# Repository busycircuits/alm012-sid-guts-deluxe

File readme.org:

* ALM012 SID GUTS DELUXE

[[ALM012.png]]

** Introduction

The MOS Technology 6581/8580 ‘Sound Interface Device’ chip, aka the ‘SID’, was the sound generator chip used in the Commodore 64 home computer – the greatest selling home computer of all time.  The SID, by the means of 3 wavetable oscillators, a real analogue multi mode filter, an ADSR and various cross modulation options, provided the soundtrack to a generations gaming and perhaps many peoples first exposure to real sound synthesis. The SID’s unique musical aesthetic has lasted well beyond the lifetime of the C64 re-imagined in standalone products such as the SID Station and with in the computer via sophisticated software emulation.

The ALM Busy Circuits ‘SID GUTS DELUXE’ takes the legendary SID chip and brings it into the eurorack modular environment. By use of a real (or emulated) SID chip the classic sound is taken in a new direction with the levels of direct and voltage control only a modular system can offer.

The module features voltage control over numerous SID parameters including the classic PWM, Filter type, cut off, resonance and external input, waveform selection, secondary mod oscillator with ring and sync modulation, voltage per octave tracking and a 3 voice chord mode with inversion. 

The ‘SID GUTS DELUXE’ improves upon the original SID GUTS and was originally released 2014. In 2024 we ended production and have made the firmware and design files open source for anyone to build their own derivative. The files are available in this repository. 

Note you will need a donor SID chip for the module to work. Any real SID chip should work as should most emulated clones (Swin Sid etc). 

*PLEASE NOTE EVERYTHING IS PROVIDED AS IS. WE ARE UNABLE PROVIDE ANY SUPPORT TO ANYONE ATTEMPTING TO USE THESE FILES*

** Building and flashing the firmware

You'll need a basic 'usbtiny' AVR programmer.

You'll need to install avr-gcc and avrdude.

/(On mac using brew..)/
#+BEGIN_SRC
brew tap osx-cross/avr
brew install avr-gcc
brew install avrdude
#+END_SRC

Type 'make' in the firmare/ directory to compile the source code and
then run 'make ispload' (with your programmer connected) to program the
SID GUTS.

** License

Code: MIT license.

Hardware: cc-by-sa-3.0

** Guidelines for derivative works

*ALM is a registered trademark.*

The name "ALM" should not be used on any of the derivative works you create from these files.

We kindly ask to do not name any derivatives 'SID GUTS' but give it a new name.

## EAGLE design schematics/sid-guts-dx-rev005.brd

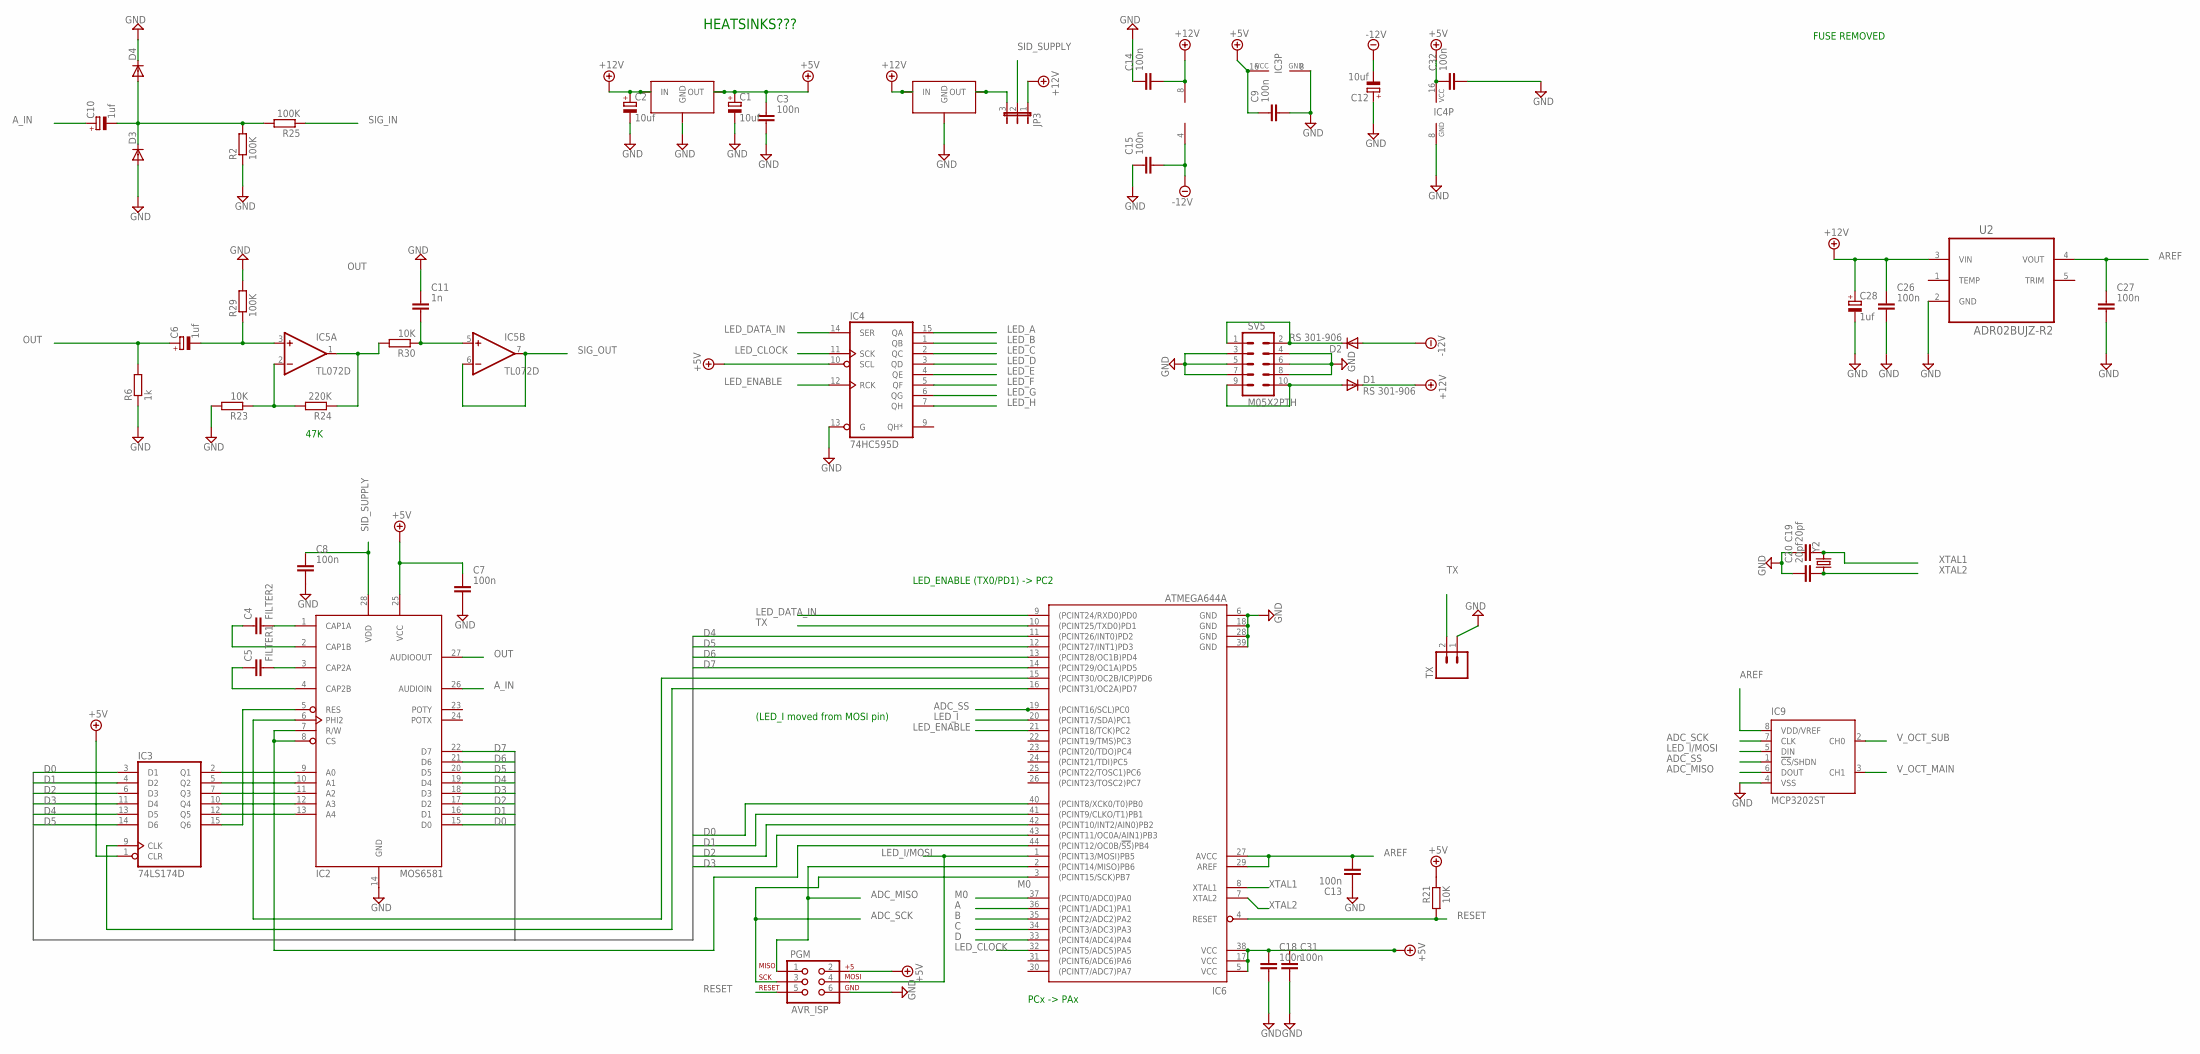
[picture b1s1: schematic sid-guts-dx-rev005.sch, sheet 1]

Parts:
C1, C2, C12: 10uf; PANASONIC_B
C3, C7, C8, C9, C13, C14, C15, C18, C26, C27, C31, C32: 100n; C0603
C4: FILTER2; C050-025X075
C5: FILTER1; C050-025X075
C6, C10, C28: 1uf; PANASONIC_B
C11: 1n; C0603
C19, C20: 20pf; C0603
D1, D2: RS 301-906; SMB-DIODE
D3, D4: DIODE-SOD123; SOD123
IC2: MOS6581; DIP-28
IC3: 74LS174D; SO16
IC4: 74HC595D; SO16
IC5: TL072D; SO08
IC6: ATMEGA644A; TQFP44
IC9: MCP3202ST; TSSOP8
JP3: JP2E; JP2
PGM: AVR_ISP; 2X3
R2, R25, R29: 100K; R0603
R6: 1k; R0603
R21, R23, R30: 10K; R0603
R24: 220K; R0603
SV5: M05X2PTH; AVR_ICSP
TX: M02PTH; 1X02
U2: ADR02BUJZ-R2; SOT95P280X100-5N
U3: 7805; VREG-7805-DPAK2
U4: 7905; VREG-7805-DPAK2
Y2: CRYSTALSMD; HC49UP

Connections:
+5V: C1.+, C3.1, C7.1, C9.1, C18.1, C31.1, C32.1, IC2.25 (VCC), IC3.1 (CLR), IC3.16 (VCC), IC4.10 (SCL), IC4.16 (VCC), IC6.5 (VCC), IC6.17 (VCC), IC6.38 (VCC), PGM.2, R21.2, U3.VOUT (OUT); also elsewhere on the board
+12V: C2.+, C14.2, C26.1, C28.+, D1.C, IC5.8 (V+), JP3.1, U2.3 (VIN), U3.VIN (IN), U4.VIN (IN); also elsewhere on the board
-12V: C12.-, C15.2, D2.A, IC5.4 (V-); also elsewhere on the board
A: IC6.36 ((PCINT1/ADC1)PA1); also elsewhere on the board
ADC_MISO: IC6.2 ((PCINT14/MISO)PB6), IC9.6 (DOUT), PGM.1
ADC_SCK: IC6.3 ((PCINT15/SCK)PB7), IC9.7 (CLK), PGM.3
ADC_SS: IC6.19 ((PCINT16/SCL)PC0), IC9.1 (!CS!/SHDN)
AREF: C13.2, C27.1, IC6.27 (AVCC), IC6.29 (AREF), IC9.8 (VDD/VREF), U2.4 (VOUT)
A_IN: C10.+, IC2.26 (AUDIOIN)
B: IC6.35 ((PCINT2/ADC2)PA2); also elsewhere on the board
C: IC6.34 ((PCINT3/ADC3)PA3); also elsewhere on the board
CS/RW: IC2.7 (R/W), IC2.8 (CS), IC6.44 ((PCINT12/OC0B/!SS!)PB4)
D: IC6.33 ((PCINT4/ADC4)PA4); also elsewhere on the board
D0: IC2.15 (D0), IC3.3 (D1), IC6.40 ((PCINT8/XCK0/T0)PB0)
D1: IC2.16 (D1), IC3.4 (D2), IC6.41 ((PCINT9/CLKO/T1)PB1)
D2: IC2.17 (D2), IC3.6 (D3), IC6.42 ((PCINT10/INT2/AIN0)PB2)
D3: IC2.18 (D3), IC3.11 (D4), IC6.43 ((PCINT11/OC0A/AIN1)PB3)
D4: IC2.19 (D4), IC3.13 (D5), IC6.11 ((PCINT26/INT0)PD2)
D5: IC2.20 (D5), IC3.14 (D6), IC6.12 ((PCINT27/INT1)PD3)
D6: IC2.21 (D6), IC6.13 ((PCINT28/OC1B)PD4)
D7: IC2.22 (D7), IC6.14 ((PCINT29/OC1A)PD5)
GND: C1.-, C2.-, C3.2, C7.2, C8.2, C9.2, C11.1, C12.+, C13.1, C14.1, C15.1, C18.2, C19.1, C20.1, C26.2, C27.2, C28.-, C31.2, C32.2, D3.A, D4.C, IC2.14 (GND), IC3.8 (GND), IC4.8 (GND), IC4.13 (G), IC6.6 (GND), IC6.18 (GND), IC6.28 (GND), IC6.39 (GND), IC9.4 (VSS), PGM.6, R2.1, R6.1, R23.2, R29.2, SV5.3, SV5.4, SV5.5, SV5.6, SV5.7, SV5.8, TX.1, U2.2 (GND), U3.GND, U4.GND; also elsewhere on the board
LED_A: IC4.15 (QA); also elsewhere on the board
LED_B: IC4.1 (QB); also elsewhere on the board
LED_C: IC4.2 (QC); also elsewhere on the board
LED_CLOCK: IC4.11 (SCK), IC6.32 ((PCINT5/ADC5)PA5)
LED_D: IC4.3 (QD); also elsewhere on the board
LED_DATA_IN: IC4.14 (SER), IC6.9 ((PCINT24/RXD0)PD0)
LED_E: IC4.4 (QE); also elsewhere on the board
LED_ENABLE: IC4.12 (RCK), IC6.21 ((PCINT18/TCK)PC2)
LED_F: IC4.5 (QF); also elsewhere on the board
LED_G: IC4.6 (QG); also elsewhere on the board
LED_H: IC4.7 (QH); also elsewhere on the board
LED_I: IC6.20 ((PCINT17/SDA)PC1); also elsewhere on the board
LED_I/MOSI: IC6.1 ((PCINT13/MOSI)PB5), IC9.5 (DIN), PGM.4
M0: IC6.37 ((PCINT0/ADC0)PA0); also elsewhere on the board
unnamed: D2.C, SV5.1, SV5.2
unnamed: JP3.3, U4.VOUT (OUT)
unnamed: D1.A, SV5.9, SV5.10
unnamed: C4.2, IC2.1 (CAP1A)
unnamed: C4.1, IC2.2 (CAP1B)
unnamed: C5.2, IC2.3 (CAP2A)
unnamed: C5.1, IC2.4 (CAP2B)
unnamed: IC2.9 (A0), IC3.2 (Q1)
unnamed: IC2.10 (A1), IC3.5 (Q2)
unnamed: IC2.11 (A2), IC3.7 (Q3)
unnamed: IC2.12 (A3), IC3.10 (Q4)
unnamed: IC2.13 (A4), IC3.12 (Q5)
unnamed: IC2.5 (RES), IC3.15 (Q6)
unnamed: IC5.1 (OUT), R24.1, R30.2
unnamed: IC3.9 (CLK), IC6.16 ((PCINT31/OC2A)PD7)
unnamed: C6.-, IC5.3 (+IN), R29.1
unnamed: IC5.2 (-IN), R23.1, R24.2
unnamed: IC2.6 (PHI2), IC6.15 ((PCINT30/OC2B/ICP)PD6)
unnamed: C10.-, D3.C, D4.A, R2.2, R25.2
unnamed: C11.2, IC5.5 (+IN), R30.1
OUT: C6.+, IC2.27 (AUDIOOUT), R6.2
RESET: IC6.4 (RESET), PGM.5, R21.1
SID_SUPPLY: C8.1, IC2.28 (VDD), JP3.2
SIG_IN: R25.1; also elsewhere on the board
SIG_OUT: IC5.6 (-IN), IC5.7 (OUT); also elsewhere on the board
TX: IC6.10 ((PCINT25/TXD0)PD1), TX.2
V_OCT_MAIN: IC9.3 (CH1); also elsewhere on the board
V_OCT_SUB: IC9.2 (CH0); also elsewhere on the board
XTAL1: C19.2, IC6.8 (XTAL1), Y2.2
XTAL2: C20.2, IC6.7 (XTAL2), Y2.1

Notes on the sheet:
47K
PCx -> PAx
FUSE REMOVED
HEATSINKS???
(LED_I moved from MOSI pin)
LED_ENABLE (TX0/PD1) -> PC2

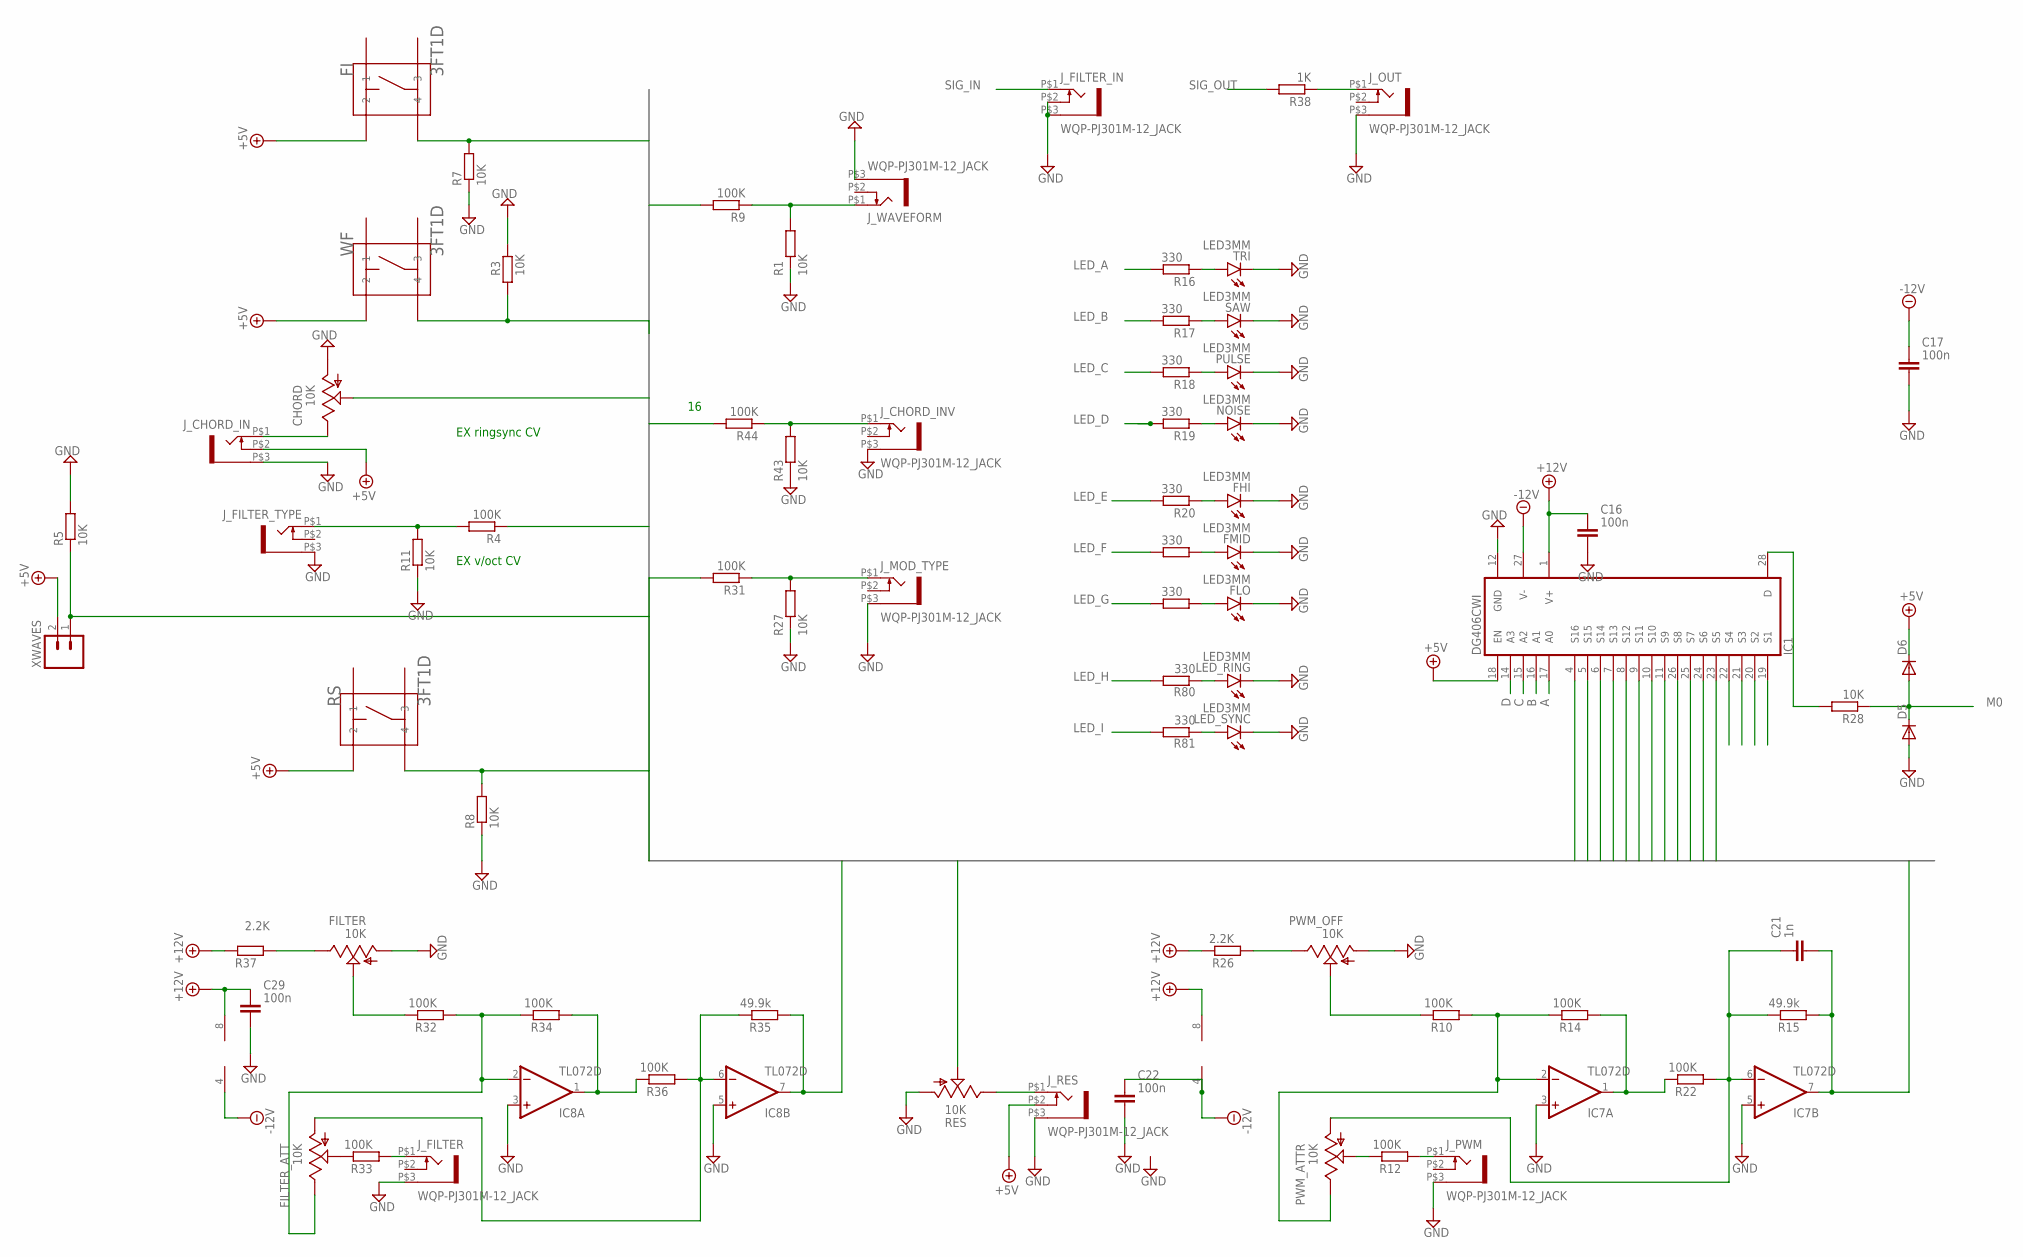
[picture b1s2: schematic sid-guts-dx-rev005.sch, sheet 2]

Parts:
C16, C17, C22, C29: 100n; C0603
C21: 1n; C0603
CHORD: 10K; EVUF
D5, D6: DIODE-SOD123; SOD123
FHI: LED3MM
FI: 3FT1D; 3FT
FILTER: 10K; EVUF
FILTER_ATT: 10K; EVUF
FLO: LED3MM
FMID: LED3MM
IC1: DG406CWI; SO28L
IC7, IC8: TL072D; SO08
J_CHORD_IN: WQP-PJ301M-12_JACK
J_CHORD_INV: WQP-PJ301M-12_JACK
J_FILTER: WQP-PJ301M-12_JACK
J_FILTER_IN: WQP-PJ301M-12_JACK
J_FILTER_TYPE: WQP-PJ301M-12_JACK
J_MOD_TYPE: WQP-PJ301M-12_JACK
J_OUT: WQP-PJ301M-12_JACK
J_PWM: WQP-PJ301M-12_JACK
J_RES: WQP-PJ301M-12_JACK
J_WAVEFORM: WQP-PJ301M-12_JACK
LED_RING: LED3MM
LED_SYNC: LED3MM
NOISE: LED3MM
PULSE: LED3MM
PWM_ATTR: 10K; EVUF
PWM_OFF: 10K; EVUF
R1, R3, R5, R7, R8, R11, R27, R28, R43: 10K; R0603
R4, R9, R10, R12, R14, R22, R31, R32, R33, R34, R36, R44: 100K; R0603
R15, R35: 49.9k; R0603
R16, R17, R18, R19, R20, R80, R81, R82, R83: 330; R0603
R26, R37: 2.2K; R0603
R38: 1K; R0603
RES: 10K; EVUF
RS: 3FT1D; 3FT
SAW: LED3MM
TRI: LED3MM
WF: 3FT1D; 3FT
XWAVES: M02PTH; 1X02

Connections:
+5V: D6.C, FI.P$2 (2), IC1.18 (EN), J_CHORD_IN.P$2 (3), J_RES.P$2 (3), RS.P$2 (2), WF.P$2 (2), XWAVES.2; also elsewhere on the board
+12V: C16.1, C29.1, IC1.1 (V+), IC7.8 (V+), IC8.8 (V+), R26.2, R37.2; also elsewhere on the board
-12V: C17.1, C22.1, IC1.27 (V-), IC7.4 (V-), IC8.4 (V-); also elsewhere on the board
A: IC1.17 (A0); also elsewhere on the board
B: IC1.16 (A1); also elsewhere on the board
C: IC1.15 (A2); also elsewhere on the board
D: IC1.14 (A3); also elsewhere on the board
EXP1: IC1.22 (S4)
EXP3: IC1.20 (S2)
EXP5: IC1.21 (S3)
EXP6: IC1.19 (S1)
GND: C16.2, C17.2, C22.2, C29.2, CHORD.1 (A), D5.A, FHI.K (C), FILTER.1 (A), FLO.K (C), FMID.K (C), IC1.12 (GND), IC7.3 (+IN), IC7.5 (+IN), IC8.3 (+IN), IC8.5 (+IN), J_CHORD_IN.P$3 (1), J_CHORD_INV.P$3 (1), J_FILTER.P$3 (1), J_FILTER_IN.P$2 (3), J_FILTER_IN.P$3 (1), J_FILTER_TYPE.P$3 (1), J_MOD_TYPE.P$3 (1), J_OUT.P$3 (1), J_PWM.P$3 (1), J_RES.P$3 (1), J_WAVEFORM.P$3 (1), LED_RING.K (C), LED_SYNC.K (C), NOISE.K (C), PULSE.K (C), PWM_OFF.1 (A), R1.1, R3.2, R5.2, R7.1, R8.1, R11.1, R27.1, R43.1, RES.1 (A), SAW.K (C), TRI.K (C); also elsewhere on the board
I5: C21.2, IC1.23 (S5), IC7.7 (OUT), R15.1
I6: IC1.24 (S6), RES.2 (S)
I7: IC1.25 (S7), IC8.7 (OUT), R35.1
I8: FI.P$4 (4), IC1.26 (S8), R7.2
I9: IC1.11 (S9), R5.1, XWAVES.1
I10: IC1.10 (S10), R8.2, RS.P$4 (4)
I11: IC1.9 (S11), R4.1
I12: CHORD.2 (S), IC1.8 (S12)
I13: IC1.7 (S13), R9.2
I14: IC1.6 (S14), R3.1, WF.P$4 (4)
I15: IC1.5 (S15), R31.2
I16: IC1.4 (S16), R44.2
LED_A: R16.2; also elsewhere on the board
LED_B: R17.2; also elsewhere on the board
LED_C: R18.2; also elsewhere on the board
LED_D: R19.2; also elsewhere on the board
LED_E: R20.2; also elsewhere on the board
LED_F: R83.2; also elsewhere on the board
LED_G: R82.2; also elsewhere on the board
LED_H: R80.2; also elsewhere on the board
LED_I: R81.2; also elsewhere on the board
M0: D5.C, D6.A, R28.1; also elsewhere on the board
unnamed: FHI.A, R20.1
unnamed: CHORD.3 (E), J_CHORD_IN.P$1 (2)
unnamed: FMID.A, R83.1
unnamed: FLO.A, R82.1
unnamed: IC1.28 (D), R28.2
unnamed: J_WAVEFORM.P$1 (2), R1.2, R9.1
unnamed: LED_RING.A, R80.1
unnamed: LED_SYNC.A, R81.1
unnamed: J_FILTER_TYPE.P$1 (2), R4.2, R11.2
unnamed: J_RES.P$1 (2), RES.3 (E)
unnamed: PWM_OFF.2 (S), R10.2
unnamed: IC7.2 (-IN), PWM_ATTR.3 (E), R10.1, R14.2
unnamed: R16.1, TRI.A
unnamed: R17.1, SAW.A
unnamed: PULSE.A, R18.1
unnamed: NOISE.A, R19.1
unnamed: J_PWM.P$1 (2), R12.1
unnamed: PWM_ATTR.2 (S), R12.2
unnamed: IC7.1 (OUT), R14.1, R22.2
unnamed: C21.1, IC7.6 (-IN), PWM_ATTR.1 (A), R15.2, R22.1
unnamed: PWM_OFF.3 (E), R26.1
unnamed: J_MOD_TYPE.P$1 (2), R27.2, R31.1
unnamed: FILTER.2 (S), R32.2
unnamed: FILTER_ATT.3 (E), IC8.2 (-IN), R32.1, R34.2
unnamed: J_FILTER.P$1 (2), R33.1
unnamed: IC8.1 (OUT), R34.1, R36.2
unnamed: FILTER_ATT.1 (A), IC8.6 (-IN), R35.2, R36.1
unnamed: FILTER.3 (E), R37.1
unnamed: J_OUT.P$1 (2), R38.1
unnamed: FILTER_ATT.2 (S), R33.2
unnamed: J_CHORD_INV.P$1 (2), R43.2, R44.1
SIG_IN: J_FILTER_IN.P$1 (2); also elsewhere on the board
SIG_OUT: R38.2; also elsewhere on the board

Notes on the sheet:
EX v/oct CV
EX ringsync CV

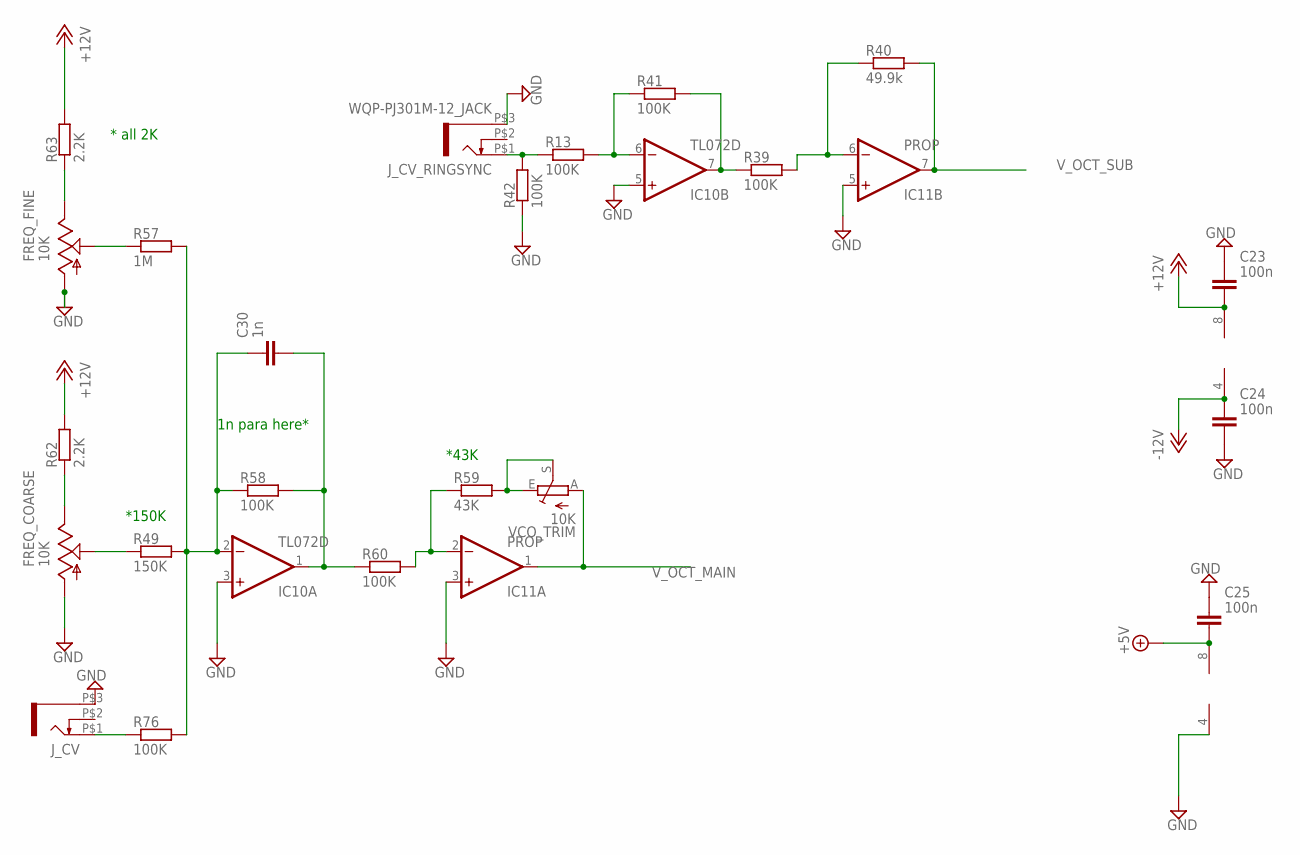
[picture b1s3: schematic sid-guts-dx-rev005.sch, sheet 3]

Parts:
C23, C24, C25: 100n; C0603
C30: 1n; C0603
FREQ_COARSE: 10K; EVUF
FREQ_FINE: 10K; EVUF
IC10: TL072D; SO08
IC11: PROP; SO08
J_CV: WQP-PJ301M-12_JACK
J_CV_RINGSYNC: WQP-PJ301M-12_JACK
R13, R39, R41, R42, R58, R60, R76: 100K; R0603
R40: 49.9k; R0603
R49: 150K; R0603
R57: 1M; R0603
R59: 43K; R0603
R62, R63: 2.2K; R0603
VCO_TRIM: 10K; S64YW

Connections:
+5V: C25.2, IC11.8 (V+); also elsewhere on the board
+12V: C23.2, IC10.8 (V+), R62.2, R63.2; also elsewhere on the board
-12V: C24.1, IC10.4 (V-); also elsewhere on the board
GND: C23.1, C24.2, C25.1, FREQ_COARSE.1 (A), FREQ_FINE.1 (A), IC10.3 (+IN), IC10.5 (+IN), IC11.3 (+IN), IC11.4 (V-), IC11.5 (+IN), J_CV.P$3 (1), J_CV_RINGSYNC.P$3 (1), R42.1; also elsewhere on the board
unnamed: IC10.7 (OUT), R39.1, R41.2
unnamed: IC10.6 (-IN), R13.2, R41.1
unnamed: J_CV_RINGSYNC.P$1 (2), R13.1, R42.2
unnamed: IC11.6 (-IN), R39.2, R40.1
unnamed: J_CV.P$1 (2), R76.1
unnamed: FREQ_COARSE.2 (S), R49.1
unnamed: C30.1, IC10.2 (-IN), R49.2, R57.2, R58.1, R76.2
unnamed: FREQ_FINE.2 (S), R57.1
unnamed: C30.2, IC10.1 (OUT), R58.2, R60.1
unnamed: IC11.2 (-IN), R59.1, R60.2
unnamed: R59.2, VCO_TRIM.E, VCO_TRIM.S
unnamed: FREQ_COARSE.3 (E), R62.1
unnamed: FREQ_FINE.3 (E), R63.1
V_OCT_MAIN: IC11.1 (OUT), VCO_TRIM.A; also elsewhere on the board
V_OCT_SUB: IC11.7 (OUT), R40.2; also elsewhere on the board

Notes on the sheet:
*43K
* all 2K
1n para here*
*150K

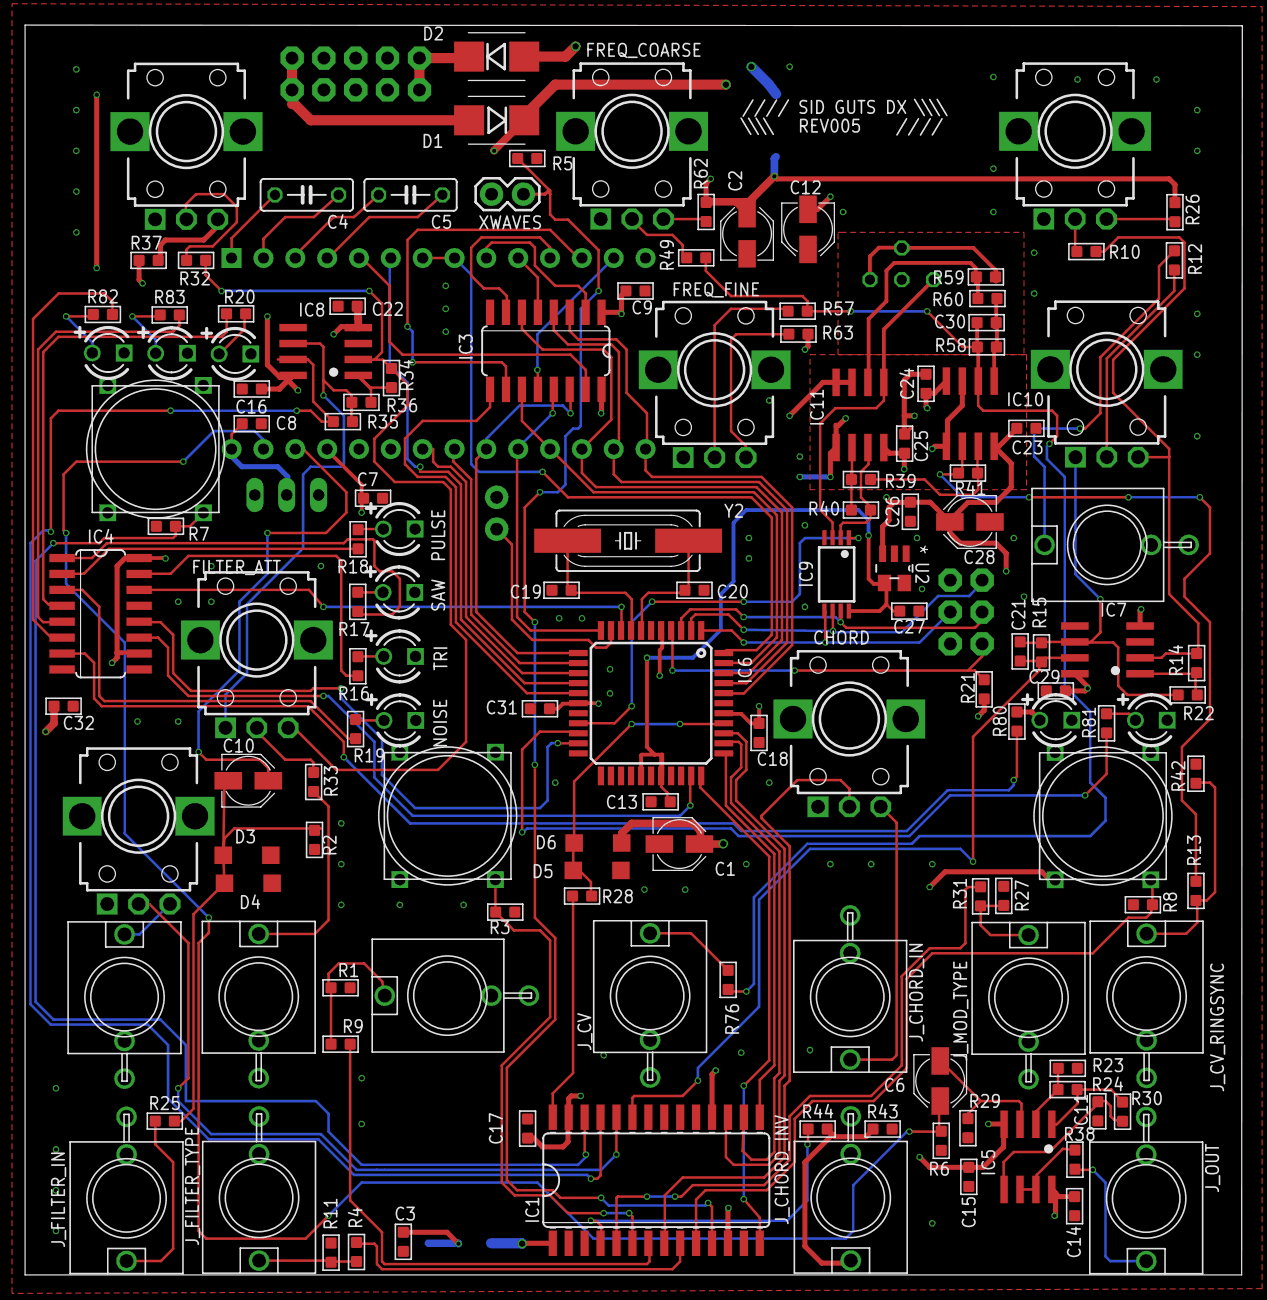
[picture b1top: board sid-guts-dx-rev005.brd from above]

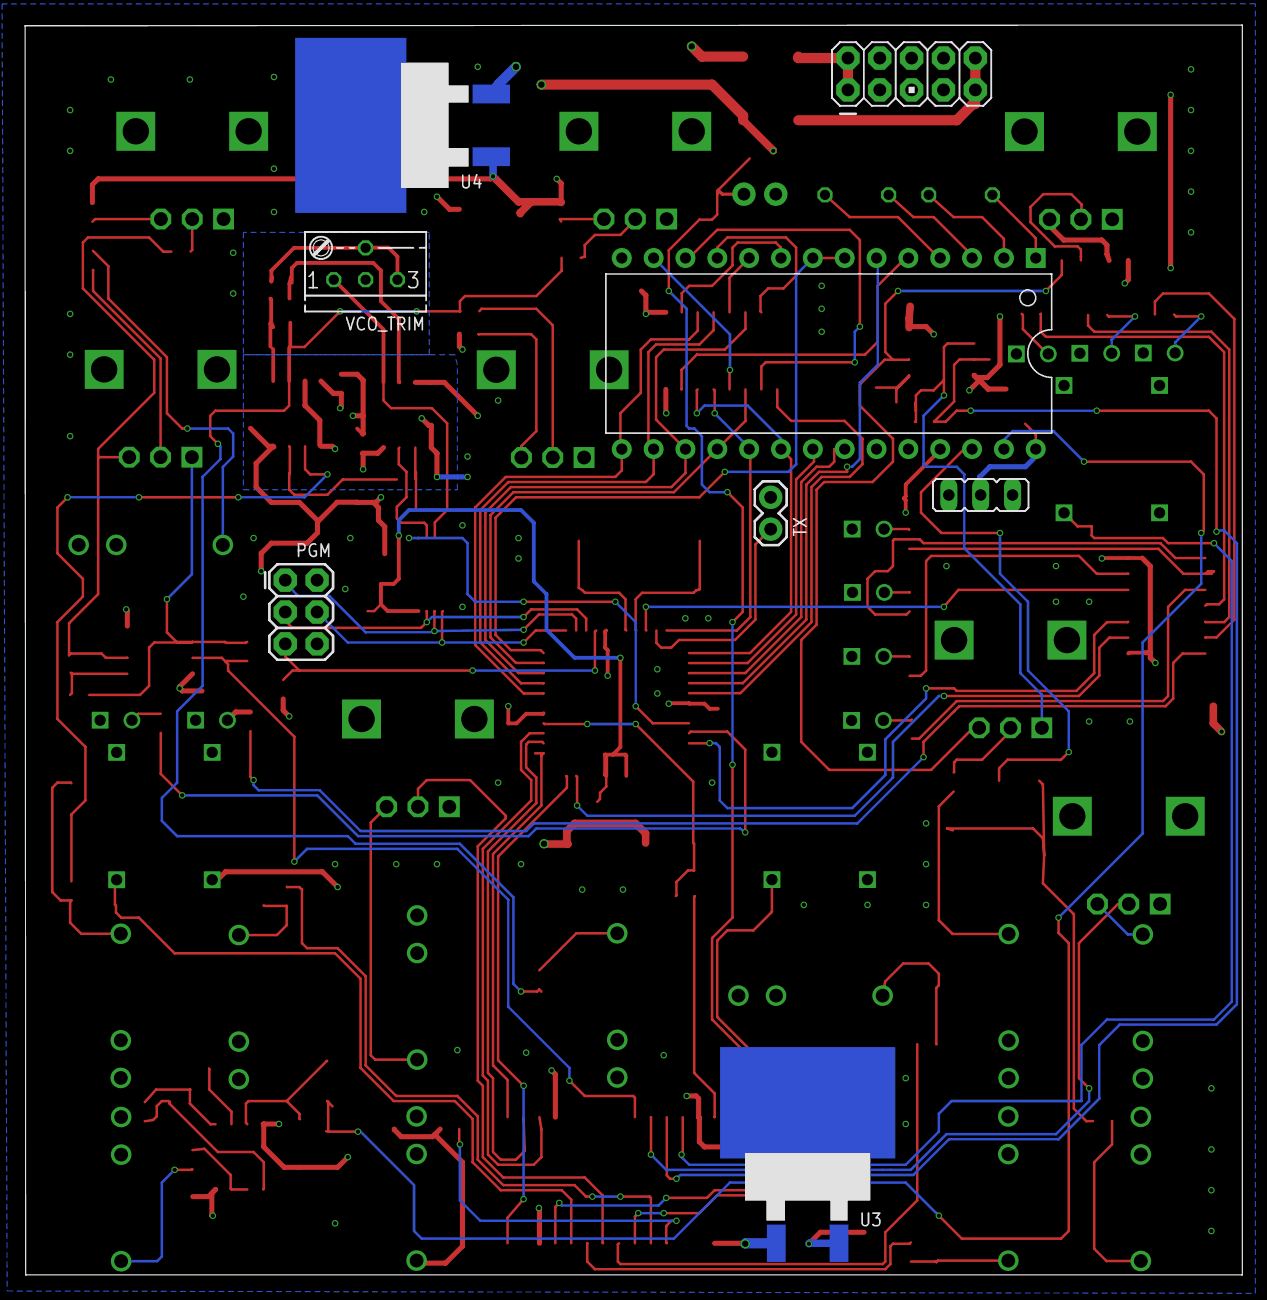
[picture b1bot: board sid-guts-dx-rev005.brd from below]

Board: 4 copper layers, 97.1 x 99.7 mm, 147 parts (8 on the bottom side), 122 nets.

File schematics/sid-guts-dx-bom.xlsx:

Qty | Parts | Value | Device | Package | SOLDERED REAR | Description / Notes | Mouser Part Num | RS Part Num | Other Part Num
7 | CHORD, FILTER, FILTER_ATT, FREQ_COARSE, PWM_ATTR, PWM_OFF, RES | 10K | ALPHA-9MMA | EVUF |  | 9 mm Square Rotary Potentiometers
1 | FREQ_FINE | 10K | ALPHA-9MMA |  |  | knurled 9 mm Square Rotary Potentiometer
1 | VCO_TRIM | 10K | TRIM_1234-S64YW | S64YW | Y | Trimmer | 72-T93YB-10K
22 | R2, R4, R9, R10, R12, R13, R14, R22, R25, R29, R31, R32, R33, R34, R36, R39, R4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 | 100K | RESISTOR0603 | R0603
1 | R49 | 150k | RESISTOR0603 | R0603
12 | R1, R3, R5, R7, R8, R11, R21, R23, R27, R28, R30, R43 | 10K | RESISTOR0603 | R0603
1 | R24 | 200K | RESISTOR0603 | R0603
9 | R80, R81, R82, R83, R16, R17, R18, R19, R20 | 330 | RESISTOR0603 | R0603
4 | R26, R37, R63, R62 | 2.2K | RESISTOR0603 | R0603
1 | R38 | 1K | RESISTOR0603 | R0603
1 | R57 | 1M | RESISTOR0603 | R0603
1 | R6 | 1k | RESISTOR0603 | R0603
3 | R15, R35, R40 | 49.9k | RESISTOR0603 | R0603
1 | R59 | 43K | RESISTOR0603 | R0603
19 | C3, C7, C8, C9, C13, C14, C15, C16, C17, C18, C22, C23, C24, C25, C26, C27, C29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 | 100n | CAPACITOR0603 | C0603
3 | C30, C11, C21 | 1n | CAPACITOR0603 | C0603
3 | C6, C10, C28 | 1uf | CPOL-EUB | PANASONIC_B |  | POLARIZED CAPACITOR, European symbol
3 | C1, C2, C12 | 10uf | CPOL-EUB | PANASONIC_B |  | POLARIZED CAPACITOR, European symbol
2 | C19, C20 | 18pf | CAPACITOR0603 | C0603
1 | IC4 | 74HC595D | 74HC595D | SO16 |  | 8-bit SHIFT REGISTER, output latch | 511-M74HC595YRM13TR
1 | IC3 | 74LS174D | 74LS174D | SO16 |  | Hex D type FLIP FLOP, clear |  |  | Farnell 175-0034
1 | IC6 | ATMEGA644A | ATMEGA644A | TQFP44 |  | ATMEGA644PV-10AU |  | 715-3814 | Farnell 1972104
1 | IC1 | DG406CWI | DG406CWI | SO28L |  | ANALOG MULTIPLEXER | 781-DG406DW-E3
4 | IC5, IC7, IC8, IC10 | TL072D | TL072D | SO08 |  | OP AMP | 595-TL072CDR
1 | IC9 | MCP3202ST | MCP3202ST | TSSOP8 |  | MCP3202-CI/ST Dual Channel 12-Bit A/D Converter with SPI Serial Interface | 579-MCP3202-CI/ST
1 | IC2 | SOCKET | MOS6581 | DIL-28 | Y | DIL-28 Wide SOCKET - No IC |  |  | Rapid 22-0115
1 | IC11 | PROP | AD8532 | SO08 |  | OP AMP | 584-AD8532ARZ-R
1 | U3 | 7805 | VREG-7805-DPAK2 | VREG-7805-DPAK2 | Y |  |  | 714-0657
1 | U4 | 7809 | VREG-7809-DPAK2 | VREG-7809-DPAK2 | Y |  | 511-L7809CD2T-TR
1 | U2 | ADR02BUJZ-R2 | ADR02BUJZ-R2 | TSOT-5 ? |  | ADR02BUJZ-R2 Ultracompact, Precision 5.0 Voltage References |  |  | This should be ADR02AUJZ-REEL7
2 | D1, D2 | RS 301-906 | DIODESMB | SMB-DIODE |  | Diode | 621-B130LB-F
2 | D3, D4, |  | DIODE-SOD123 | SOD123 |  | DIODE |  | 700-3671
2 | D5, D6 |  |  | SOD123 |  | Diode | 512-MBR0520L
9 | FHI, FLO, FMID, LED_RING, LED_SYNC, NOISE, PULSE, SAW, TRI | LED3MM | LED3MM | LED3MM |  | All RED except NOISE green, TRI yellow, SAW orange
1 | SV5 | M05X2PTH | M05X2PTH |  | Y | Header 5x2
1 | Y2 |  | CRYSTALSMD | HC49UP |  | 16 Mhz Crystal |  |  | Farnell 184-2294
1 | JP3 |  | JP3E | JP3 | Y | 3 Pin header for jumper
2 | C4, C5 |  |  |  | Y | Capacitor SOCKET - 2.54MM SINGLE ROW HEADER 3 PIN with middle pin clipped.
3 | FI, RS, WF | 3FT1D | 3FT1D | 3FT |  | Mulitmec - 3FT1D
12 | J_CHORD_INV, J_CV_RINGSYNC, J_FILTER, J_FILTER_IN, J_MOD_TYPE, J_OUT, J_PWM, J_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 | WQP-PJ301M-12_JACK | WQP-PJ301M-12_JACK | WQP-PJ301M-12_JACK |  | Jacks
2 | TX, XWAVES |  | M02PTH | 1X02 |  | NOT NEEDED
1 | PGM | AVR_ISP | AVR_SPI_PRG_6PTH | 2X3 |  | NOT NEEDED

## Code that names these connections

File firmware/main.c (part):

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#define PIN_MULT_B PIN_A2 
#define PIN_MULT_C PIN_A3
#define PIN_MULT_D PIN_A4 
#define PIN_LED_I      PIN_C1 
#define PIN_LED_DATA   PIN_D0
#define PIN_LED_CLOCK  PIN_A5
#define PIN_LED_ENABLE PIN_C2
#define PIN_TX PIN_D1

#define PIN_ADC_MOSI     PIN_B5
#define PIN_ADC_MISO     PIN_B6
#define PIN_ADC_SPICLOCK PIN_B7
#define PIN_ADC_SLAVE_SELECT PIN_C0

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void mcp3202_init()
{
  uu_pin_mode(PIN_ADC_MOSI, OUTPUT);
  uu_pin_mode(PIN_ADC_MISO, INPUT);
  uu_pin_mode(PIN_ADC_SPICLOCK, OUTPUT);
  uu_pin_mode(PIN_ADC_SLAVE_SELECT, OUTPUT);
}
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  //read bits from adc
  for (int i=11; i>=0; i--)
    {
      adcvalue += uu_pin_digital_read(PIN_ADC_MISO)<<i;
      //cycle clock
      uu_pin_digital_write(PIN_ADC_SPICLOCK, HIGH);
      uu_pin_digital_write(PIN_ADC_SPICLOCK, LOW);
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  byte shift_mask = mask & 0xFF;

  if (mask & LED_SYNC)
    uu_pin_digital_write(PIN_LED_I, HIGH);
  else
    uu_pin_digital_write(PIN_LED_I, LOW);

  uu_pin_digital_write(PIN_LED_ENABLE, LOW);
  uu_pin_shift_out(PIN_LED_DATA, PIN_LED_CLOCK, MSBFIRST, shift_mask);  
  uu_pin_digital_write(PIN_LED_ENABLE, HIGH);
}

int analog_read()
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  int c, i = 0;

  PORTD = 0;
  PORTB = 0x10;   // PB4 is high to disable Chip Select
  DDRD  = 0xFE;   // Keep RxD as an input, everything else output
  DDRB  = 0xFF;

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
  uu_usart_init();
  
  uu_pin_mode(PIN_LED_I, OUTPUT);

  uu_pin_mode(PIN_MULT_IN, INPUT);

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  uu_pin_mode(PIN_MULT_D, OUTPUT);

  uu_pin_mode(PIN_LED_DATA, OUTPUT);
  uu_pin_mode(PIN_LED_CLOCK, OUTPUT);
  uu_pin_mode(PIN_LED_ENABLE, OUTPUT);
  
  /* Initialise Timer 0 OC0A to 1MHz on Pin 6. */
  TIMSK2 = 0;
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
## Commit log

2024-05-01 fix image ref and typo
2024-05-01 more cleanups
2024-05-01 and more misc cleanups...
2024-05-01 fix version typo in source

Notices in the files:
firmware/main.c:
Copyright (c) 2014 ALM Co Ltd
Parts based on code written by Alexis Kotlowy, released in Public Domain.
parts and their libraries:
SparkFun: Licensing: CC v3.0 Share-Alike You are welcome to use this library for commercial purposes.
